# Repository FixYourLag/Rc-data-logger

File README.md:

# Rc-data-logger
diy rc data logger

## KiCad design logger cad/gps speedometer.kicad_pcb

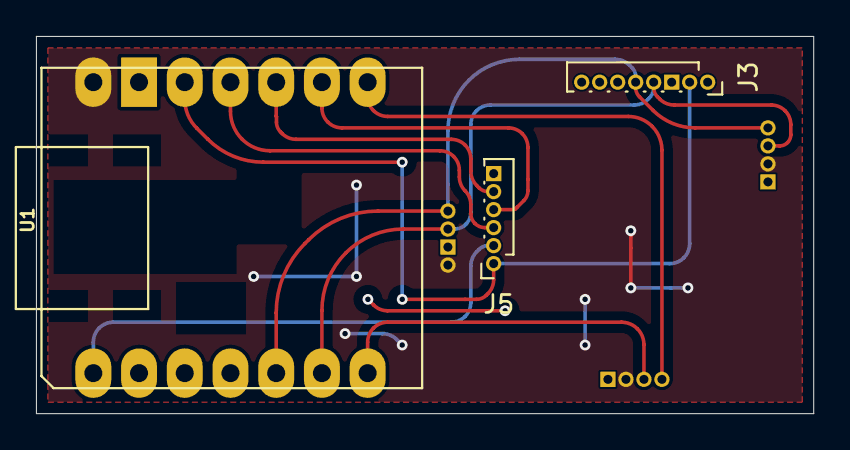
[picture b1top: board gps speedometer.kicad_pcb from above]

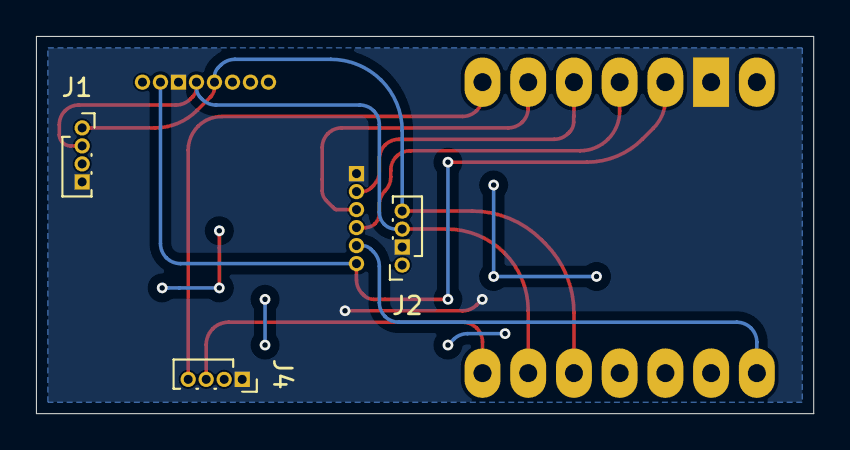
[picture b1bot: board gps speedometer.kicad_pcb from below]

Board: 2 copper layers, 43.2 x 21.0 mm, 6 parts (3 on the bottom side), 11 nets.

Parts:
J1: display; PinSocket_1x04_P1.00mm_Vertical
J2: barometer; PinSocket_1x04_P1.00mm_Vertical
J3: imu; PinSocket_1x08_P1.00mm_Vertical
J4: gps; PinSocket_1x04_P1.00mm_Vertical
J5: sd card; PinSocket_1x06_P1.00mm_Vertical
U1: MOUDLE-SEEEDUINO-XIAO-ESP32S3; MOUDLE14P-SMD-2.54-21X17.8MM

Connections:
GND: J1.4, J2.2, J3.3, J4.1, J5.6, U1.13 (GND)
VCC: J1.3, J2.1, J4.2, U1.14 (5V)
VDD: J3.2, J5.1, U1.12 (3V3)
cs: J5.2, U1.1 (PA02_A0_D0)
miso: J5.5, U1.10 (PA5_A9_D9_MISO)
mosi: J5.3, U1.11 (PA6_A10_D10_MOSI)
rx: J4.4, U1.8 (PB09_D7_RX)
scl: J1.2, J2.3, J3.4, U1.6 (PA9_A5_D5_SCL)
sclk: J5.4, U1.9 (PA7_A8_D8_SCK)
sda: J1.1, J2.4, J3.5, U1.5 (PA8_A4_D4_SDA)
tx: J4.3, U1.7 (PB08_A6_TX)

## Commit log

2024-04-25 add .ino file
    code so far
2024-04-25 reupload
2024-04-25 add kicad files
2024-04-27 refactoring
